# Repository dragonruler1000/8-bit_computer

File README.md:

# 8-bit_computer
This is a 8-bit computer baised on the version that ben eater made on a breadboard. <br>
I made it so i could learn more how to route pcbs and learn how computers work on a more detailed level. <br>
It is programed by the dip switches the 4 possition is for addres and the 8 possition is for instruction/data.
# Usage instructions
more detailed instructions are going to be added after i get the pc built and the microcode working.
# pictures
Full 3D model<br>

PCB 3d model

PCB

Case 3d model <br/>

Case is split into two with each part being the same just rotated 180 degrees</br>
Schematic:

# BOM

| Quantity | Value                            | Unit Price $ | Total price $ | price with coupns | Link                                                                                                                                  | running total | running total with coupons | notes                                                 | Customer number |
|----------|----------------------------------|--------------|---------------|-------------------|---------------------------------------------------------------------------------------------------------------------------------------|---------------|----------------------------|-------------------------------------------------------|-----------------|
| 10       | 1k resistor                      | 0.0074       | 0.074         | 0.074             | https://www.lcsc.com/product-detail/C172669.html                                                                                      | 0.08          | 0.08                       |                                                       | 1               |
| 10       | 10k resistor                     | 0.03         | 0.3           | 0.3               | https://www.jameco.com/webapp/wcs/stores/servlet/ProductDisplay?storeId=10001&langId=-1&catalogId=10001&productId=691104              | 0.4           | 0.4                        | order in multibles of ten                             | 2               |
| 1        | 100k resistor                    | 0.0072       | 0.0072        | 0.0072            | https://www.lcsc.com/product-detail/C1367560.html                                                                                     | 0.41          | 0.41                       |                                                       | 3               |
| 30       | 470 resisrer                     | 0.0333       | 0.999         | 0.999             | https://www.lcsc.com/product-detail/C1369132.html?s_z=h_Passives%257CResistors%257CThrough%2520Hole%2520Resistors                     | 1.47          | 1.47                       | order in multibles of ten                             | 4               |
| 1        | 1M resistor                      | 0.1          | 0.1           | 0.1               | https://www.digikey.com/en/products/detail/stackpole-electronics-inc/CF14JT1M00/1741316                                               | 1.58          | 1.58                       |                                                       | 5               |
| 1        | 1M potentiometer                 | 1.23         | 1.23          | 1.23              | https://www.jameco.com/webapp/wcs/stores/servlet/ProductDisplay?storeId=10001&langId=-1&catalogId=10001&productId=2161422             | 2.88          | 2.88                       |                                                       | 6               |
| 10       | 0.01 uF cap                      | 0.2475       | 2.475         | 2.475             | https://www.lcsc.com/product-detail/C710551.html?s_z=n_DE2E3SA103MN7AT02F                                                             | 5.5           | 5.5                        | order in multibles of five                            | 7               |
| 70       | 0.1 uf cap                       | 0.0502       | 3.514         | 3.514             | https://www.lcsc.com/product-detail/C2693793.html                                                                                     | 9.22          | 9.22                       | order in multibles of ten                             | 8               |
| 1        | 1 uf cap                         | 0.0434       | 0.0434        | 0.0434            | https://www.lcsc.com/product-detail/C1620550.html                                                                                     | 9.27          | 9.27                       | order in multibles of ten                             | 9               |
| 5        | 555 timer                        | 0.2706       | 1.353         | 1.353             | https://www.lcsc.com/product-detail/C129708.html?s_z=n_SA555p                                                                         | 10.7          | 10.7                       | order in multiples of five                            | 10              |
| 2        | 74LS00                           | 0.5999       | 1.1998        | 1.1998            | https://www.lcsc.com/product-detail/C181629.html?s_z=n_SN74LS00N                                                                      | 11.97         | 11.97                      |                                                       | 11              |
| 1        | 74LS02                           | 0.56         | 0.56          | 0.56              | https://www.jameco.com/webapp/wcs/stores/servlet/ProductDisplay?storeId=10001&langId=-1&catalogId=10001&productId=46287               | 12.56         | 12.56                      |                                                       | 12              |
| 5        | 74ls04                           | 0.2012       | 1.006         | 1.006             | https://www.lcsc.com/product-detail/C42395516.html?s_z=n_SN74LS04N                                                                    | 13.63         | 13.63                      |                                                       | 13              |
| 3        | 74ls08                           | 0.4985       | 1.4955        | 1.4955            | https://www.lcsc.com/product-detail/C2869595.html?s_z=n_SN74LS08N                                                                     | 15.22         | 15.22                      |                                                       | 14              |
| 1        | 74ls32                           | 0.5979       | 0.5979        | 0.5979            | https://www.lcsc.com/product-detail/C2865704.html?s_z=n_SN74LS32N                                                                     | 15.85         | 15.85                      |                                                       | 15              |
| 1        | 74ls107                          | 1.0539       | 1.0539        | 1.0539            | https://www.lcsc.com/product-detail/C22466323.html                                                                                    | 16.97         | 16.97                      |                                                       | 16              |
| 2        | 74ls86                           | 0.62         | 1.24          | 1.24              | https://www.jameco.com/webapp/wcs/stores/servlet/ProductDisplay?storeId=10001&langId=-1&catalogId=10001&pa=48098&productId=48098      | 18.28         | 18.28                      |                                                       | 17              |
| 1        | 74LS138                          | 0.81         | 0.81          | 0.81              | https://www.jameco.com/webapp/wcs/stores/servlet/ProductDisplay?storeId=10001&langId=-1&catalogId=10001&productId=46607               | 19.14         | 19.14                      |                                                       | 18              |
| 1        | 74LS139                          | 0.75         | 0.75          | 0.75              | https://www.jameco.com/webapp/wcs/stores/servlet/ProductDisplay?storeId=10001&langId=-1&catalogId=10001&productId=46623               | 19.94         | 19.94                      |                                                       | 19              |
| 1        | 74LS157                          | 0.4148       | 0.4148        | 0.4148            | https://www.lcsc.com/product-detail/C2863363.html?s_z=n_74LS157                                                                       | 20.38         | 20.38                      |                                                       | 20              |
| 2        | 74ls161                          | 0.5363       | 1.0726        | 1.0726            | https://www.lcsc.com/product-detail/C609766.html?s_z=n_74LS161                                                                        | 21.52         | 21.52                      |                                                       | 21              |
| 8        | 74ls173                          | 0.94         | 7.52          | 7.52              | https://www.jameco.com/webapp/wcs/stores/servlet/ProductDisplay?storeId=10001&langId=-1&catalogId=10001&productId=46922               | 29.49         | 29.49                      |                                                       | 22              |
| 2        | SN74189N                         | 2.984        | 5.968         | 5.968             | https://www.lcsc.com/product-detail/C1550125.html?s_z=n_SN74LS173AN                                                                   | 35.82         | 35.82                      |                                                       | 23              |
| 6        | 74ls245                          | 0.7227       | 4.3362        | 4.3362            | https://www.lcsc.com/product-detail/C7753.html?s_z=n_SN74LS245N                                                                       | 40.42         | 40.42                      |                                                       | 24              |
| 1        | 74ls273                          | 0.7659       | 0.7659        | 0.7659            | https://www.lcsc.com/product-detail/C2879026.html?s_z=n_SN74LS273N                                                                    | 41.23         | 41.23                      |                                                       | 25              |
| 5        | 74ls283                          | 0.3261       | 1.6305        | 1.6305            | https://www.lcsc.com/product-detail/C968685.html                                                                                      | 42.96         | 42.96                      |                                                       | 26              |
| 3        | AT28C64B-15PU                    | 5.5          | 16.5          | 16.5              | https://www.digikey.com/en/products/detail/microchip-technology/AT28C64B-15PU/1008529?s=N4IgTCBcDaIIIBUwA4DCA2ALAIQLQEYBWABQFUQBdAXyA | 60.45         | 60.45                      |                                                       | 27              |
| 3        | Double-throw toggle switch       | 0.616        | 1.848         | 1.848             | https://www.lcsc.com/product-detail/C2985935.html                                                                                     | 62.41         | 62.41                      |                                                       | 28              |
| 3        | Momentary 6mm tact switch        | 0.24         | 0.72          | 0.72              | https://www.jameco.com/webapp/wcs/stores/servlet/ProductDisplay?storeId=10001&langId=-1&catalogId=10001&productId=149948              | 63.17         | 63.17                      |                                                       | 29              |
| 1        | 8-position DIP switch            | 0.3944       | 0.3944        | 0.3944            | https://www.lcsc.com/product-detail/C458084.html                                                                                      | 63.59         | 63.59                      |                                                       | 30              |
| 1        | 4-position DIP switch            | 0.1623       | 0.1623        | 0.1623            | https://www.lcsc.com/product-detail/C5123702.html                                                                                     | 63.76         | 63.76                      |                                                       | 31              |
| 50       | Red LED                          | 0.0251       | 1.255         | 1.255             | https://www.lcsc.com/product-detail/C99771.html                                                                                       | 65.09         | 65.09                      | order in multibles of fifty                           | 32              |
| 10       | Yellow LED                       | 0.0324       | 0.324         | 0.324             | https://www.lcsc.com/product-detail/C20618149.html                                                                                    | 65.43         | 65.43                      | order in multibles of ten                             | 33              |
| 30       | Blue LED                         | 0.0376       | 1.128         | 1.128             | https://www.lcsc.com/product-detail/C86881.html                                                                                       | 66.63         | 66.63                      | order in multibles of ten                             | 34              |
| 20       | Green LED                        | 0.11         | 2.2           | 2.2               | https://www.jameco.com/webapp/wcs/stores/servlet/ProductDisplay?storeId=10001&langId=-1&catalogId=10001&productId=693901              | 68.96         | 68.96                      | order in multibles of ten                             | 35              |
| 4        | Common cathode 7-segment display | 1.04         | 4.16          | 4.16              | https://www.jameco.com/webapp/wcs/stores/servlet/ProductDisplay?storeId=10001&langId=-1&catalogId=10001&productId=17187               | 73.37         | 73.37                      |                                                       | 36              |
| 5        | USB-C connector                  | 0.085        | 0.425         | 0.425             | https://www.lcsc.com/product-detail/C5187470.html                                                                                     | 73.82         | 73.82                      |                                                       | 37              |
| 1        | PCB                              | 93.5         | 93.5          | 73.5              | JLCPCB.com                                                                                                                            | 172.93        | 151.73                     |                                                       | 38              |
| 1        | Shipping cost and terifs         | 64.8         | 64.8          | 64.8              |                                                                                                                                       | 241.62        | 220.42                     | maybe more then actual cost but added for transpeincy |                 |

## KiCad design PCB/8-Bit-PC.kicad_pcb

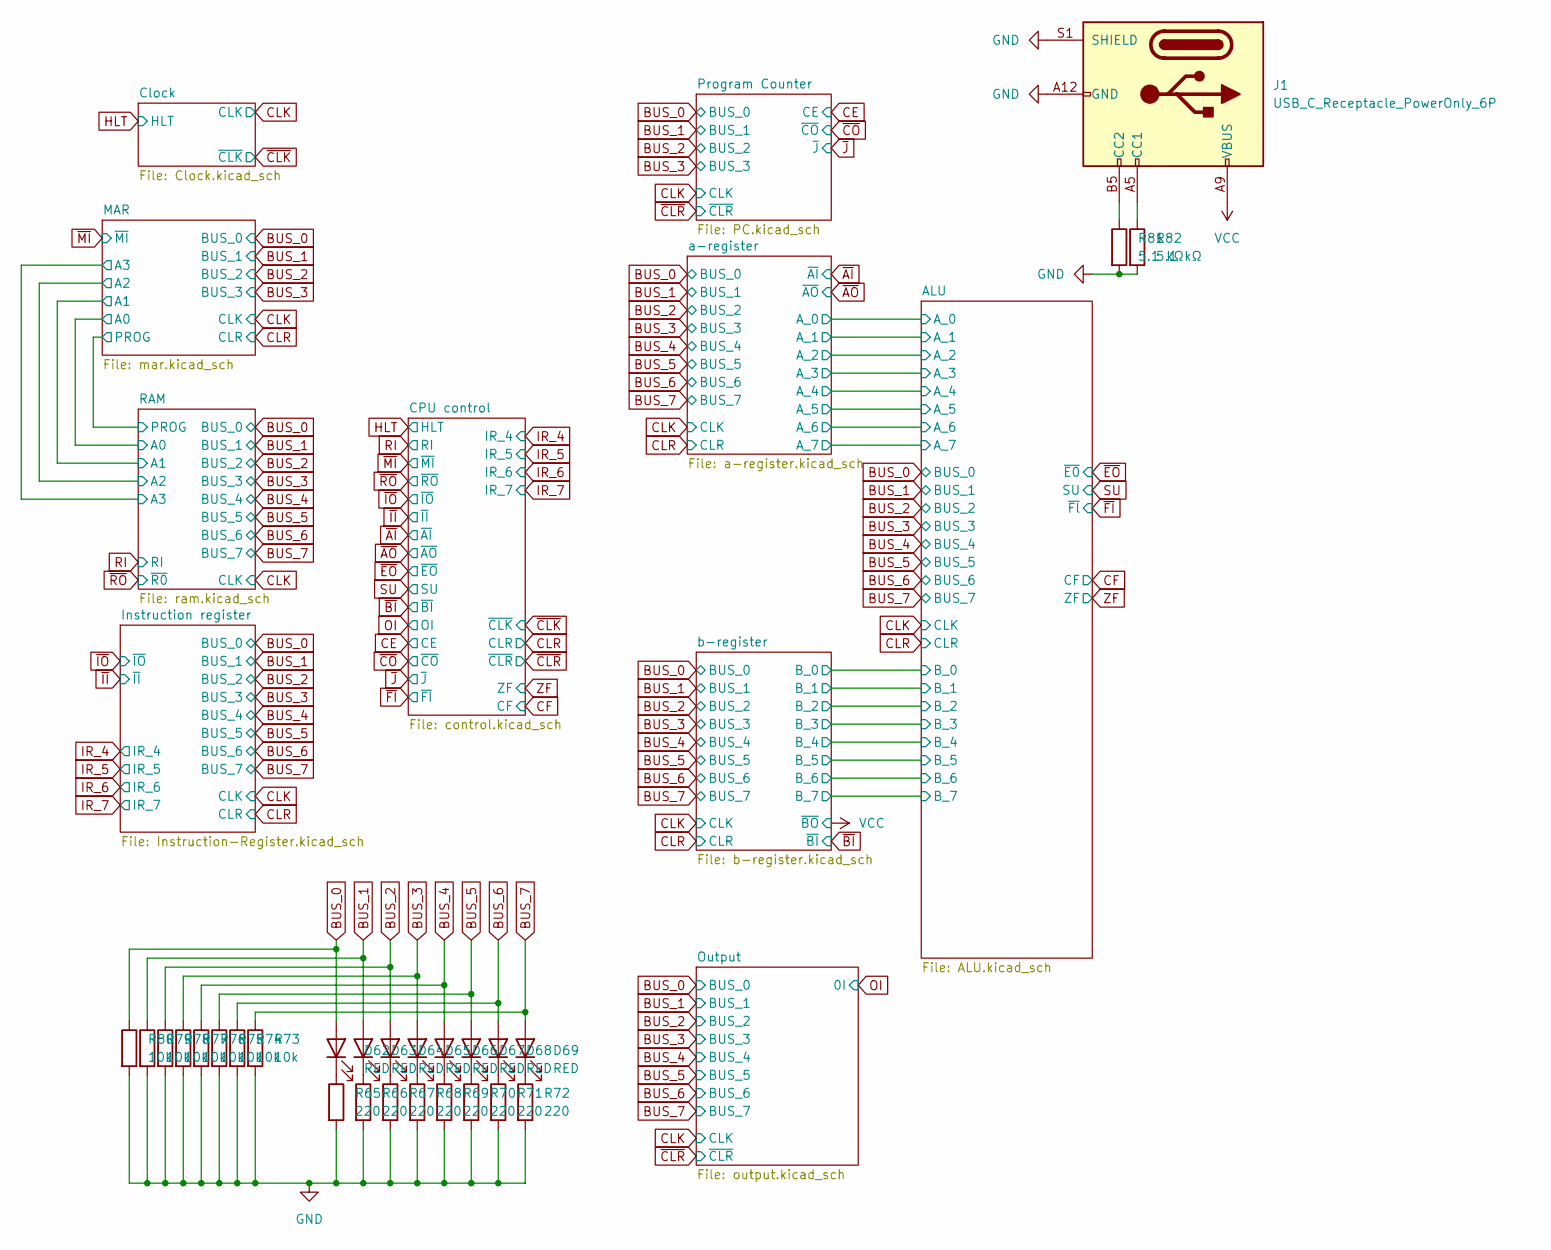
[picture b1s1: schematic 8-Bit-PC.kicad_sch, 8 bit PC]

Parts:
D62, D63, D64, D65, D66, D67, D68, D69: RED; LED_D3.0mm
J1: USB_C_Receptacle_PowerOnly_6P; USB_C_Receptacle_HRO_TYPE-C-31-M-17
R65, R66, R67, R68, R69, R70, R71, R72: 220; R_Axial_DIN0207_L6.3mm_D2.5mm_P7.62mm_Horizontal
R73, R74, R75, R76, R77, R78, R79, R80: 10k; R_Axial_DIN0207_L6.3mm_D2.5mm_P7.62mm_Horizontal
R81, R82: 5.1 kΩ; R_Axial_DIN0207_L6.3mm_D2.5mm_P7.62mm_Horizontal

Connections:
BUS_0: D62.2 (A), R80.1; also elsewhere on the board
BUS_1: D63.2 (A), R79.1; also elsewhere on the board
BUS_2: D64.2 (A), R78.1; also elsewhere on the board
BUS_3: D65.2 (A), R77.1; also elsewhere on the board
BUS_4: D66.2 (A), R76.1; also elsewhere on the board
BUS_5: D67.2 (A), R75.1; also elsewhere on the board
BUS_6: D68.2 (A), R74.1; also elsewhere on the board
BUS_7: D69.2 (A), R73.1; also elsewhere on the board
GND: J1.A12 (GND), J1.B12 (GND), J1.S1 (SHIELD), R65.2, R66.2, R67.2, R68.2, R69.2, R70.2, R71.2, R72.2, R73.2, R74.2, R75.2, R76.2, R77.2, R78.2, R79.2, R80.2, R81.2, R82.2; also elsewhere on the board
unnamed: D62.1 (K), R65.1
unnamed: D63.1 (K), R66.1
unnamed: D64.1 (K), R67.1
unnamed: D65.1 (K), R68.1
unnamed: D66.1 (K), R69.1
unnamed: D67.1 (K), R70.1
unnamed: D68.1 (K), R71.1
unnamed: D69.1 (K), R72.1
unnamed: J1.A5 (CC1), R82.1
unnamed: J1.B5 (CC2), R81.1
VCC: J1.A9 (VBUS), J1.B9 (VBUS); also elsewhere on the board

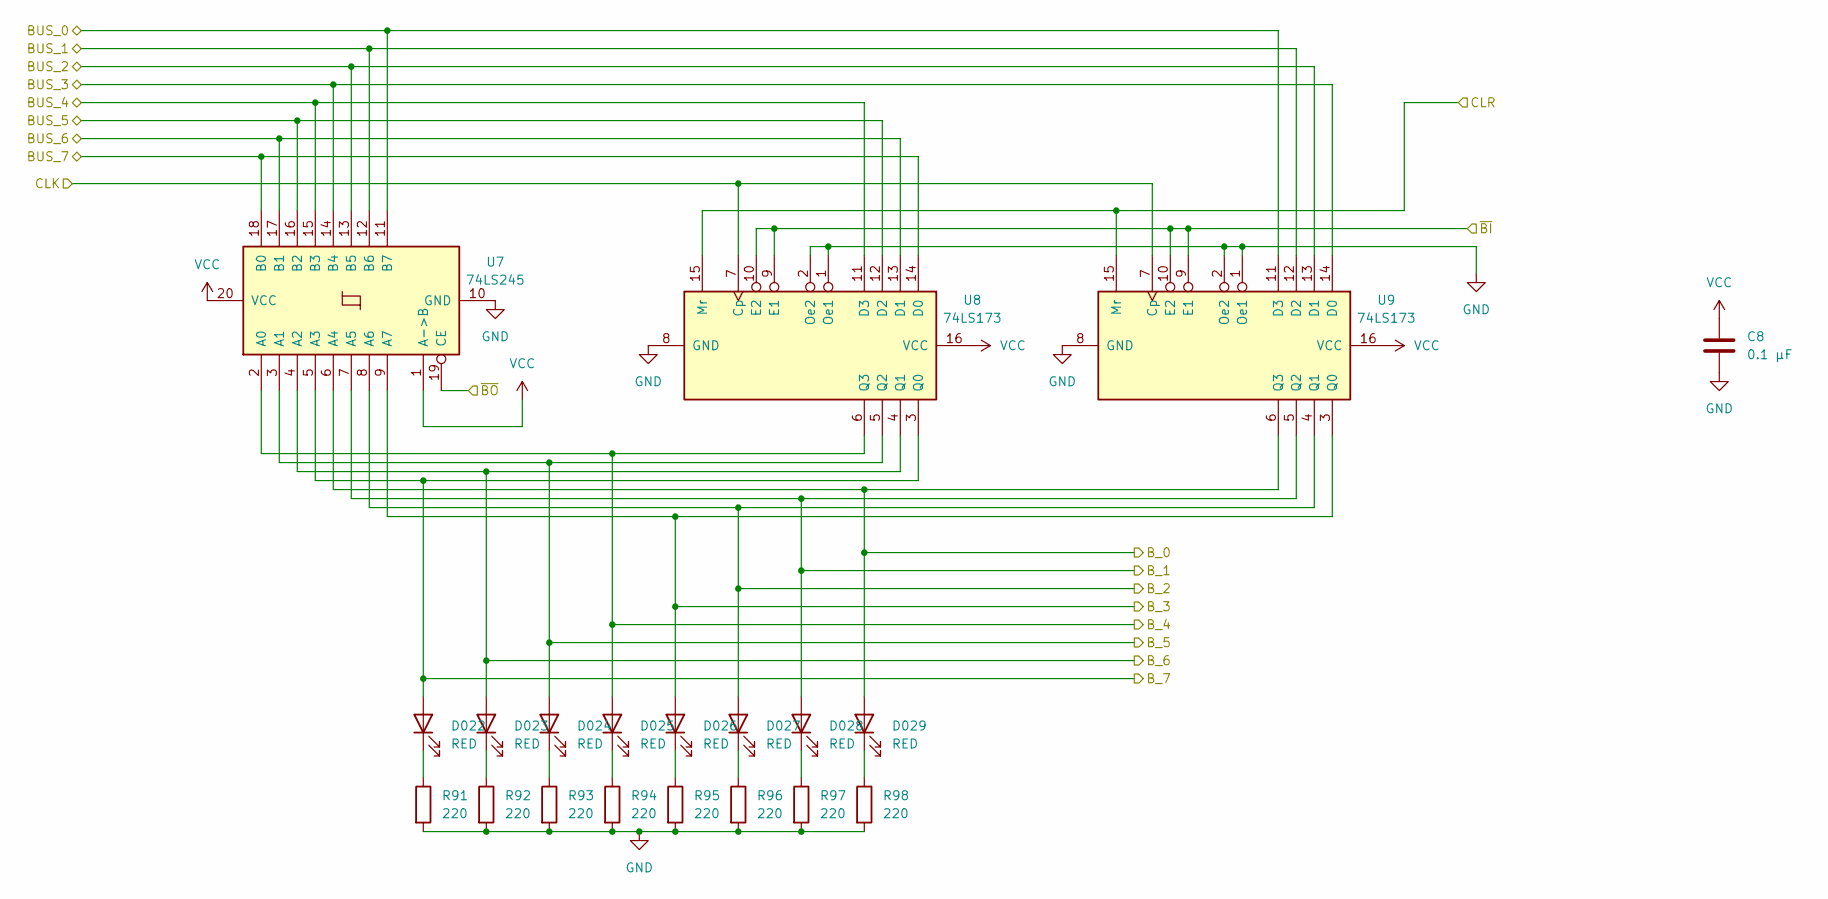
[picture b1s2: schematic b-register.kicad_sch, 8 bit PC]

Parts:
C8: 0.1 µF; C_Radial_D5.0mm_H5.0mm_P2.00mm
D022, D023, D024, D025, D026, D027, D028, D029: RED; LED_D3.0mm
R91, R92, R93, R94, R95, R96, R97, R98: 220; R_Axial_DIN0207_L6.3mm_D2.5mm_P7.62mm_Horizontal
U7: 74LS245; DIP254P762X508-20
U8, U9: 74LS173; SN74LS173AN

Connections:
/ALU/B_0: D029.2 (A), U7.6 (A4), U9.6 (Q3); also elsewhere on the board
/ALU/B_1: D028.2 (A), U7.7 (A5), U9.5 (Q2); also elsewhere on the board
/ALU/B_2: D027.2 (A), U7.8 (A6), U9.4 (Q1); also elsewhere on the board
/ALU/B_3: D026.2 (A), U7.9 (A7), U9.3 (Q0); also elsewhere on the board
/ALU/B_4: D025.2 (A), U7.2 (A0), U8.6 (Q3); also elsewhere on the board
/ALU/B_5: D024.2 (A), U7.3 (A1), U8.5 (Q2); also elsewhere on the board
/ALU/B_6: D023.2 (A), U7.4 (A2), U8.4 (Q1); also elsewhere on the board
/ALU/B_7: D022.2 (A), U7.5 (A3), U8.3 (Q0); also elsewhere on the board
BUS_0: U7.11 (B7), U9.11 (D3); also elsewhere on the board
BUS_1: U7.12 (B6), U9.12 (D2); also elsewhere on the board
BUS_2: U7.13 (B5), U9.13 (D1); also elsewhere on the board
BUS_3: U7.14 (B4), U9.14 (D0); also elsewhere on the board
BUS_4: U7.15 (B3), U8.11 (D3); also elsewhere on the board
BUS_5: U7.16 (B2), U8.12 (D2); also elsewhere on the board
BUS_6: U7.17 (B1), U8.13 (D1); also elsewhere on the board
BUS_7: U7.18 (B0), U8.14 (D0); also elsewhere on the board
CLK: U8.7 (Cp), U9.7 (Cp); also elsewhere on the board
CLR: U8.15 (Mr), U9.15 (Mr); also elsewhere on the board
GND: C8.2, R91.2, R92.2, R93.2, R94.2, R95.2, R96.2, R97.2, R98.2, U7.10 (GND), U8.1 (Oe1), U8.2 (Oe2), U8.8 (GND), U9.1 (Oe1), U9.2 (Oe2), U9.8 (GND); also elsewhere on the board
unnamed: D022.1 (K), R91.1
unnamed: D023.1 (K), R92.1
unnamed: D024.1 (K), R93.1
unnamed: D025.1 (K), R94.1
unnamed: D026.1 (K), R95.1
unnamed: D027.1 (K), R96.1
unnamed: D028.1 (K), R97.1
unnamed: D029.1 (K), R98.1
VCC: C8.1, U7.1 (A->B), U7.19 (CE), U7.20 (VCC), U8.16 (VCC), U9.16 (VCC); also elsewhere on the board
~BI: U8.9 (E1), U8.10 (E2), U9.9 (E1), U9.10 (E2); also elsewhere on the board

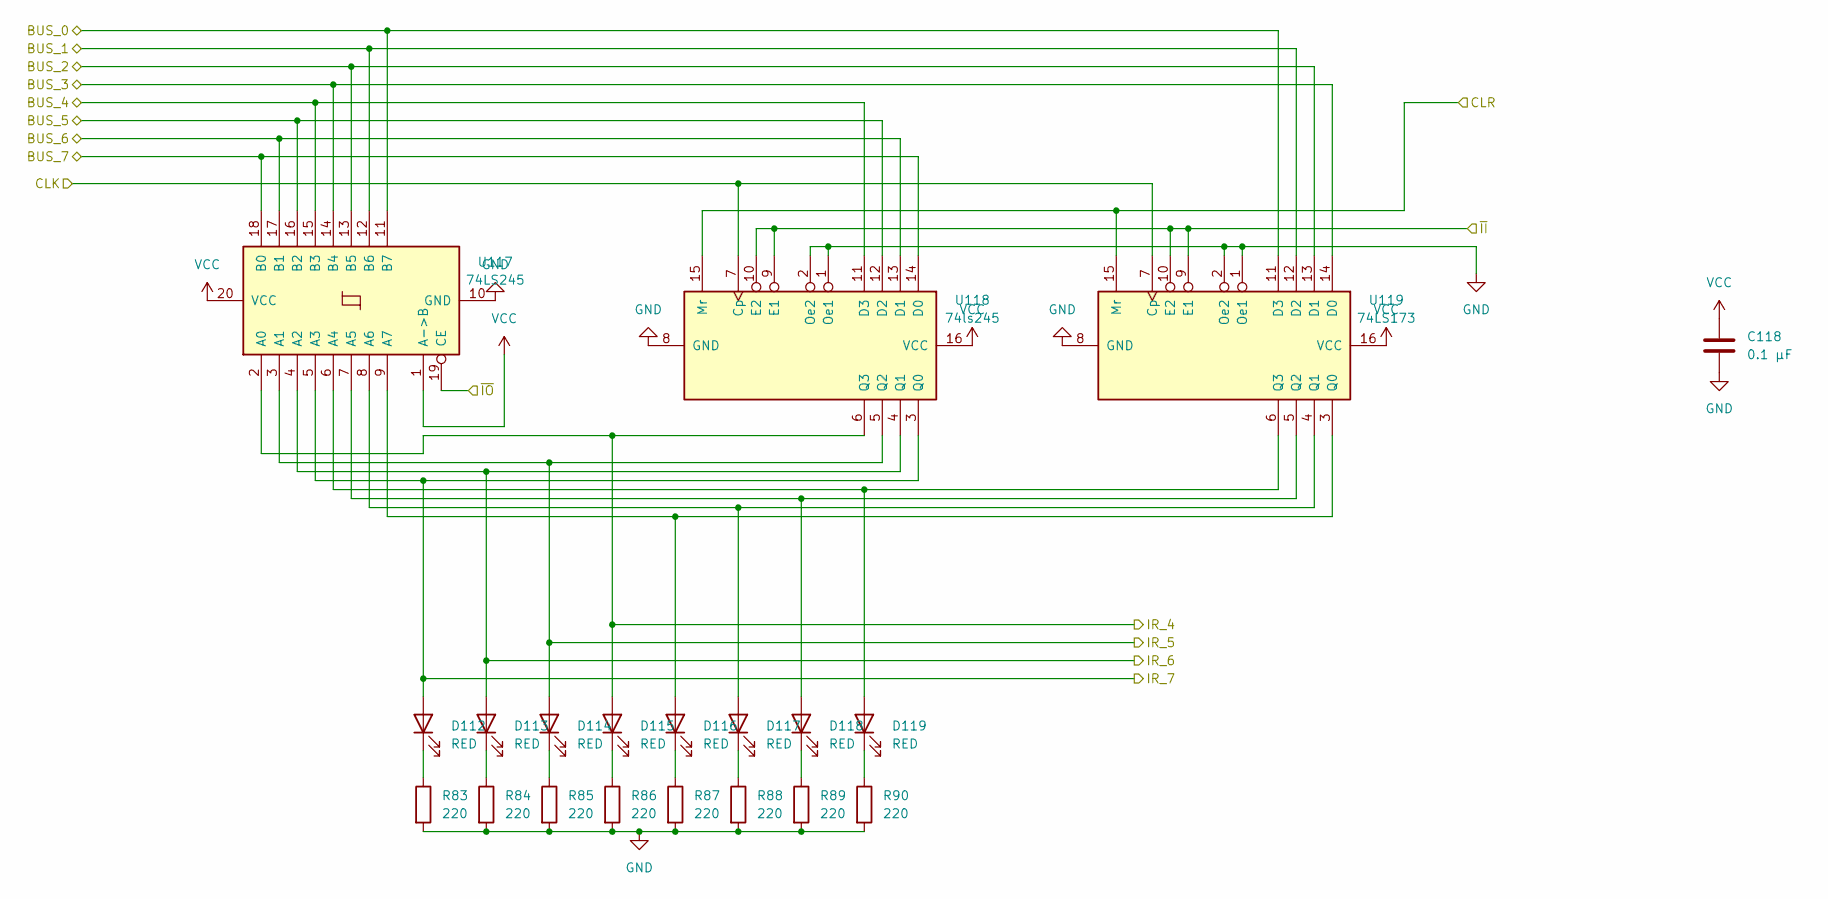
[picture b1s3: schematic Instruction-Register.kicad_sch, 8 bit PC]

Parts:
C118: 0.1 µF; C_Radial_D5.0mm_H5.0mm_P2.00mm
D112, D113, D114, D115, D116, D117, D118, D119: RED; LED_D3.0mm
R83, R84, R85, R86, R87, R88, R89, R90: 220; R_Axial_DIN0207_L6.3mm_D2.5mm_P7.62mm_Horizontal
U117: 74LS245; DIP254P762X508-20
U118: 74ls245; DIP254P762X508-20
U119: 74LS173; SN74LS173AN

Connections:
BUS_0: U117.11 (B7), U119.11 (D3); also elsewhere on the board
BUS_1: U117.12 (B6), U119.12 (D2); also elsewhere on the board
BUS_2: U117.13 (B5), U119.13 (D1); also elsewhere on the board
BUS_3: U117.14 (B4), U119.14 (D0); also elsewhere on the board
BUS_4: U117.15 (B3), U118.11 (D3); also elsewhere on the board
BUS_5: U117.16 (B2), U118.12 (D2); also elsewhere on the board
BUS_6: U117.17 (B1), U118.13 (D1); also elsewhere on the board
BUS_7: U117.18 (B0), U118.14 (D0); also elsewhere on the board
CLK: U118.7 (Cp), U119.7 (Cp); also elsewhere on the board
CLR: U118.15 (Mr), U119.15 (Mr); also elsewhere on the board
GND: C118.2, R83.2, R84.2, R85.2, R86.2, R87.2, R88.2, R89.2, R90.2, U117.10 (GND), U118.1 (Oe1), U118.2 (Oe2), U118.8 (GND), U119.1 (Oe1), U119.2 (Oe2), U119.8 (GND); also elsewhere on the board
IR_4: D115.2 (A), U117.2 (A0), U118.6 (Q3); also elsewhere on the board
IR_5: D114.2 (A), U117.3 (A1), U118.5 (Q2); also elsewhere on the board
IR_6: D113.2 (A), U117.4 (A2), U118.4 (Q1); also elsewhere on the board
IR_7: D112.2 (A), U117.5 (A3), U118.3 (Q0); also elsewhere on the board
unnamed: D112.1 (K), R83.1
unnamed: D113.1 (K), R84.1
unnamed: D114.1 (K), R85.1
unnamed: D115.1 (K), R86.1
unnamed: D116.2 (A), U117.9 (A7), U119.3 (Q0)
unnamed: D116.1 (K), R87.1
unnamed: D117.2 (A), U117.8 (A6), U119.4 (Q1)
unnamed: D117.1 (K), R88.1
unnamed: D118.2 (A), U117.7 (A5), U119.5 (Q2)
unnamed: D118.1 (K), R89.1
unnamed: D119.2 (A), U117.6 (A4), U119.6 (Q3)
unnamed: D119.1 (K), R90.1
VCC: C118.1, U117.1 (A->B), U117.20 (VCC), U118.16 (VCC), U119.16 (VCC); also elsewhere on the board
~II: U118.9 (E1), U118.10 (E2), U119.9 (E1), U119.10 (E2); also elsewhere on the board
~IO: U117.19 (CE); also elsewhere on the board

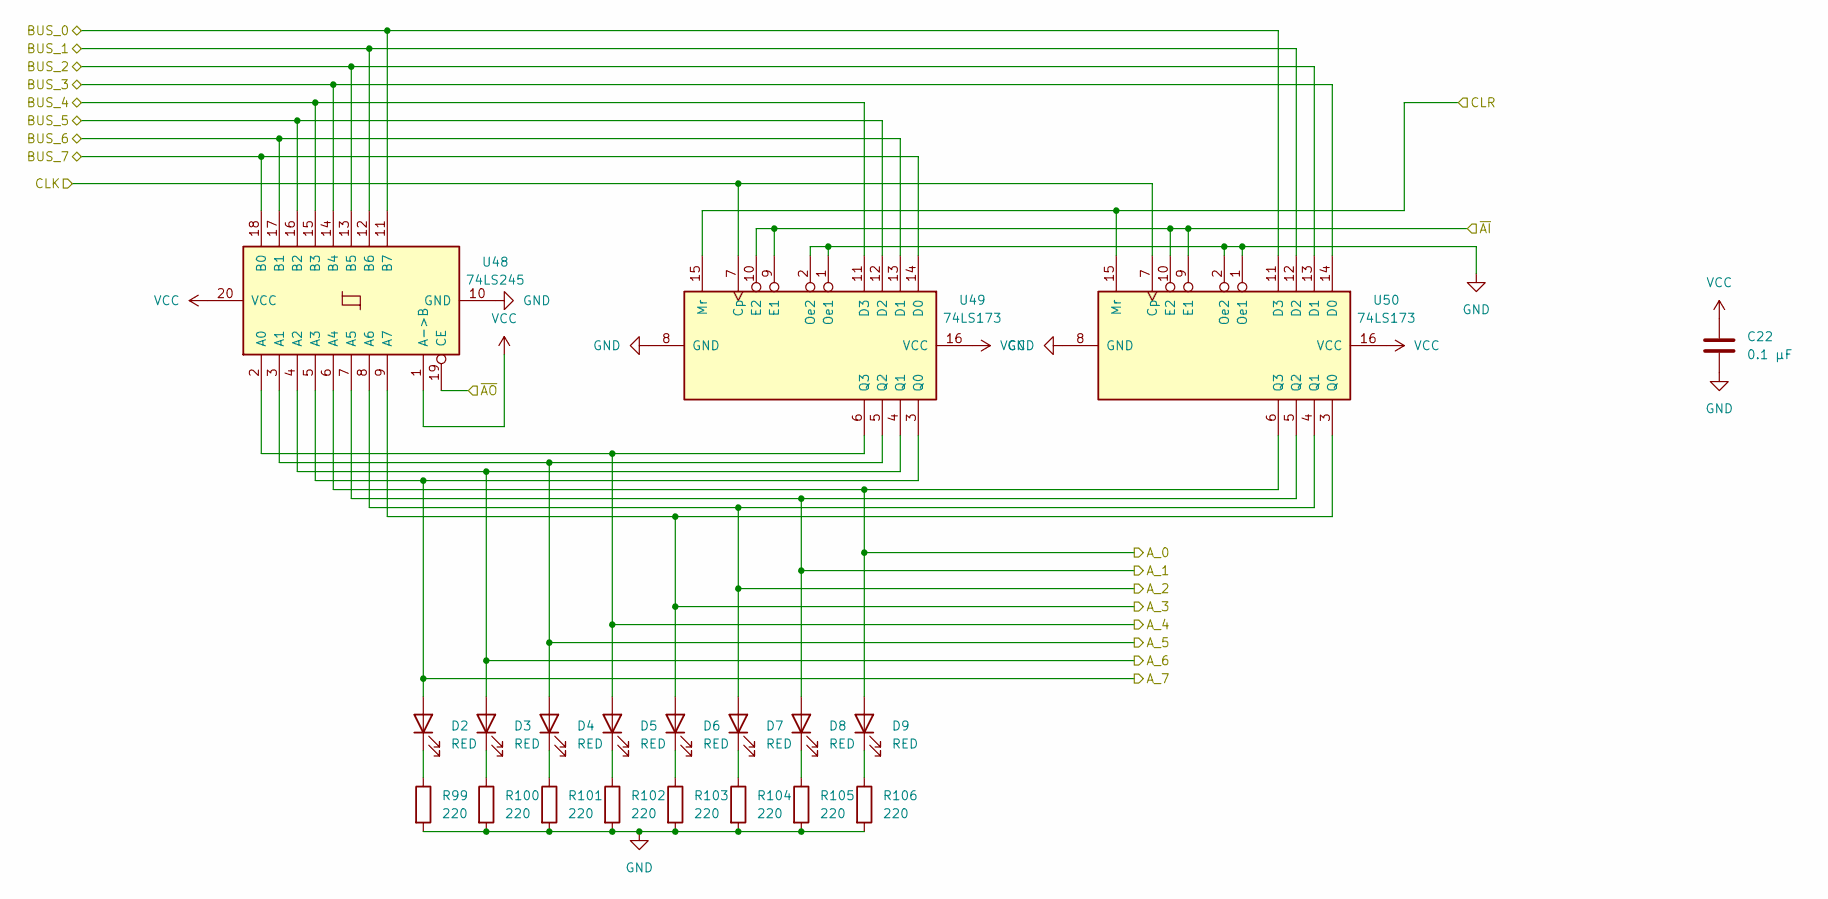
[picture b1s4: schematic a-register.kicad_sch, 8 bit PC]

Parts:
C22: 0.1 µF; C_Radial_D5.0mm_H5.0mm_P2.00mm
D2, D3, D4, D5, D6, D7, D8, D9: RED; LED_D3.0mm
R99, R100, R101, R102, R103, R104, R105, R106: 220; R_Axial_DIN0207_L6.3mm_D2.5mm_P7.62mm_Horizontal
U48: 74LS245; DIP254P762X508-20
U49, U50: 74LS173; SN74LS173AN

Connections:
/ALU/A_0: D9.2 (A), U48.6 (A4), U50.6 (Q3); also elsewhere on the board
/ALU/A_1: D8.2 (A), U48.7 (A5), U50.5 (Q2); also elsewhere on the board
/ALU/A_2: D7.2 (A), U48.8 (A6), U50.4 (Q1); also elsewhere on the board
/ALU/A_3: D6.2 (A), U48.9 (A7), U50.3 (Q0); also elsewhere on the board
/ALU/A_4: D5.2 (A), U48.2 (A0), U49.6 (Q3); also elsewhere on the board
/ALU/A_5: D4.2 (A), U48.3 (A1), U49.5 (Q2); also elsewhere on the board
/ALU/A_6: D3.2 (A), U48.4 (A2), U49.4 (Q1); also elsewhere on the board
/ALU/A_7: D2.2 (A), U48.5 (A3), U49.3 (Q0); also elsewhere on the board
BUS_0: U48.11 (B7), U50.11 (D3); also elsewhere on the board
BUS_1: U48.12 (B6), U50.12 (D2); also elsewhere on the board
BUS_2: U48.13 (B5), U50.13 (D1); also elsewhere on the board
BUS_3: U48.14 (B4), U50.14 (D0); also elsewhere on the board
BUS_4: U48.15 (B3), U49.11 (D3); also elsewhere on the board
BUS_5: U48.16 (B2), U49.12 (D2); also elsewhere on the board
BUS_6: U48.17 (B1), U49.13 (D1); also elsewhere on the board
BUS_7: U48.18 (B0), U49.14 (D0); also elsewhere on the board
CLK: U49.7 (Cp), U50.7 (Cp); also elsewhere on the board
CLR: U49.15 (Mr), U50.15 (Mr); also elsewhere on the board
GND: C22.2, R99.2, R100.2, R101.2, R102.2, R103.2, R104.2, R105.2, R106.2, U48.10 (GND), U49.1 (Oe1), U49.2 (Oe2), U49.8 (GND), U50.1 (Oe1), U50.2 (Oe2), U50.8 (GND); also elsewhere on the board
unnamed: D2.1 (K), R99.1
unnamed: D3.1 (K), R100.1
unnamed: D4.1 (K), R101.1
unnamed: D5.1 (K), R102.1
unnamed: D6.1 (K), R103.1
unnamed: D7.1 (K), R104.1
unnamed: D8.1 (K), R105.1
unnamed: D9.1 (K), R106.1
VCC: C22.1, U48.1 (A->B), U48.20 (VCC), U49.16 (VCC), U50.16 (VCC); also elsewhere on the board
~AI: U49.9 (E1), U49.10 (E2), U50.9 (E1), U50.10 (E2); also elsewhere on the board
~AO: U48.19 (CE); also elsewhere on the board

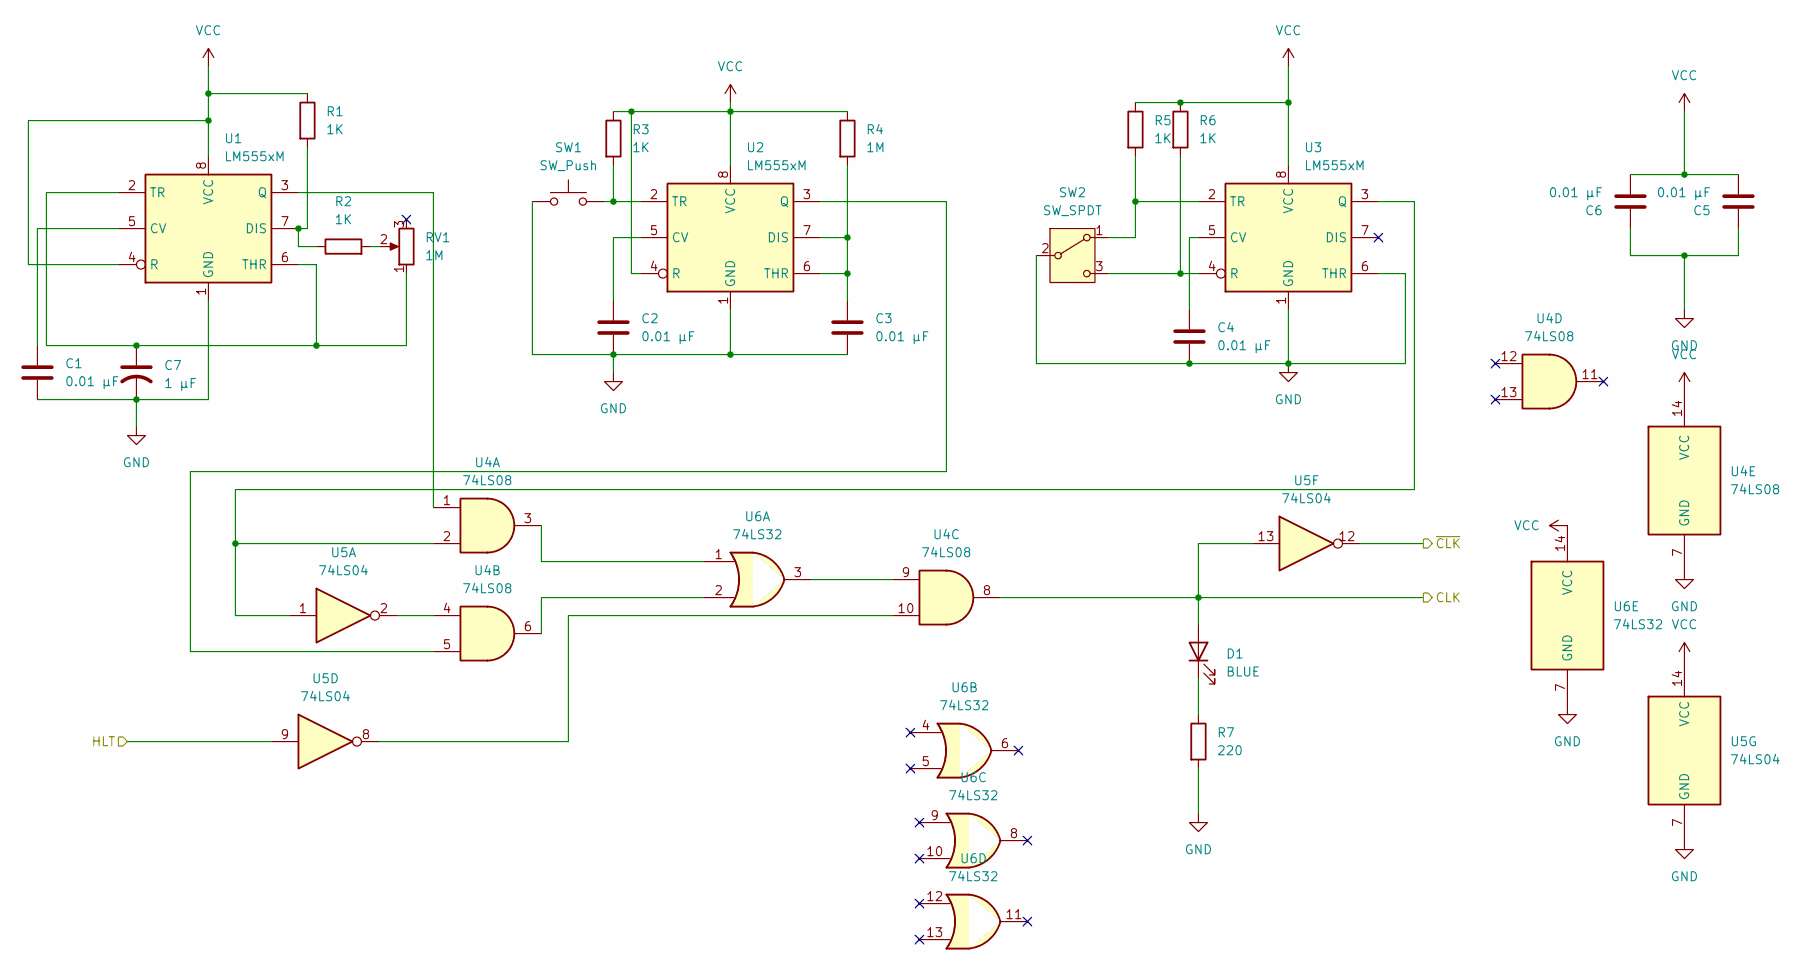
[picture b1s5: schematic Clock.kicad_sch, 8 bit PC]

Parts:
C1, C2, C3, C4, C5, C6: 0.01 µF; C_Disc_D5.0mm_W2.5mm_P2.50mm
C7: 1 µF; C_Radial_D5.0mm_H5.0mm_P2.00mm
D1: BLUE; LED_D3.0mm
R1, R2, R3, R5, R6: 1K; R_Axial_DIN0207_L6.3mm_D2.5mm_P7.62mm_Horizontal
R4: 1M; R_Axial_DIN0207_L6.3mm_D2.5mm_P7.62mm_Horizontal
R7: 220; R_Axial_DIN0207_L6.3mm_D2.5mm_P7.62mm_Horizontal
RV1: 1M; Potentiometer_Alpha_RD901F-40-00D_Single_Vertical
SW1: SW_Push; SW_PUSH_6mm
SW2: SW_SPDT; SW_SPDT_CK_JS102011SAQN
U1, U2, U3: LM555xM; SOIC-8_3.9x4.9mm_P1.27mm
U4: 74LS08; DIP-14_W7.62mm
U5: 74LS04; DIP-14_W7.62mm
U6: 74LS32; DIP-14_W7.62mm

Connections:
CLK: D1.2 (A), U4.8, U5.13; also elsewhere on the board
GND: C1.1, C2.1, C3.1, C4.1, C5.1, C6.1, C7.2, R7.2, SW1.1, SW2.2 (B), U1.1 (GND), U2.1 (GND), U3.1 (GND), U3.6 (THR), U4.7 (GND), U5.7 (GND), U6.7 (GND); also elsewhere on the board
HLT: U5.9; also elsewhere on the board
unnamed: D1.1 (K), R7.1
unnamed: R2.2, RV1.2
unnamed: R5.2, SW2.1 (A), U3.2 (TR)
unnamed: R6.2, SW2.3 (C), U3.4 (R)
unnamed: C1.2, U1.5 (CV)
unnamed: R1.2, R2.1, U1.7 (DIS)
unnamed: U1.3 (Q), U4.1
unnamed: C7.1, RV1.1, U1.2 (TR), U1.6 (THR)
unnamed: C2.2, U2.5 (CV)
unnamed: C3.2, R4.2, U2.6 (THR), U2.7 (DIS)
unnamed: U2.3 (Q), U4.5
unnamed: R3.2, SW1.2, U2.2 (TR)
unnamed: C4.2, U3.5 (CV)
unnamed: U3.3 (Q), U4.2, U5.1
unnamed: U4.3, U6.1
unnamed: U4.4, U5.2
unnamed: U4.6, U6.2
unnamed: U4.9, U6.3
unnamed: U4.10, U5.8
VCC: C5.2, C6.2, R1.1, R3.1, R4.1, R5.1, R6.1, U1.4 (R), U1.8 (VCC), U2.4 (R), U2.8 (VCC), U3.8 (VCC), U4.14 (VCC), U5.14 (VCC), U6.14 (VCC); also elsewhere on the board
~CLK: U5.12; also elsewhere on the board
